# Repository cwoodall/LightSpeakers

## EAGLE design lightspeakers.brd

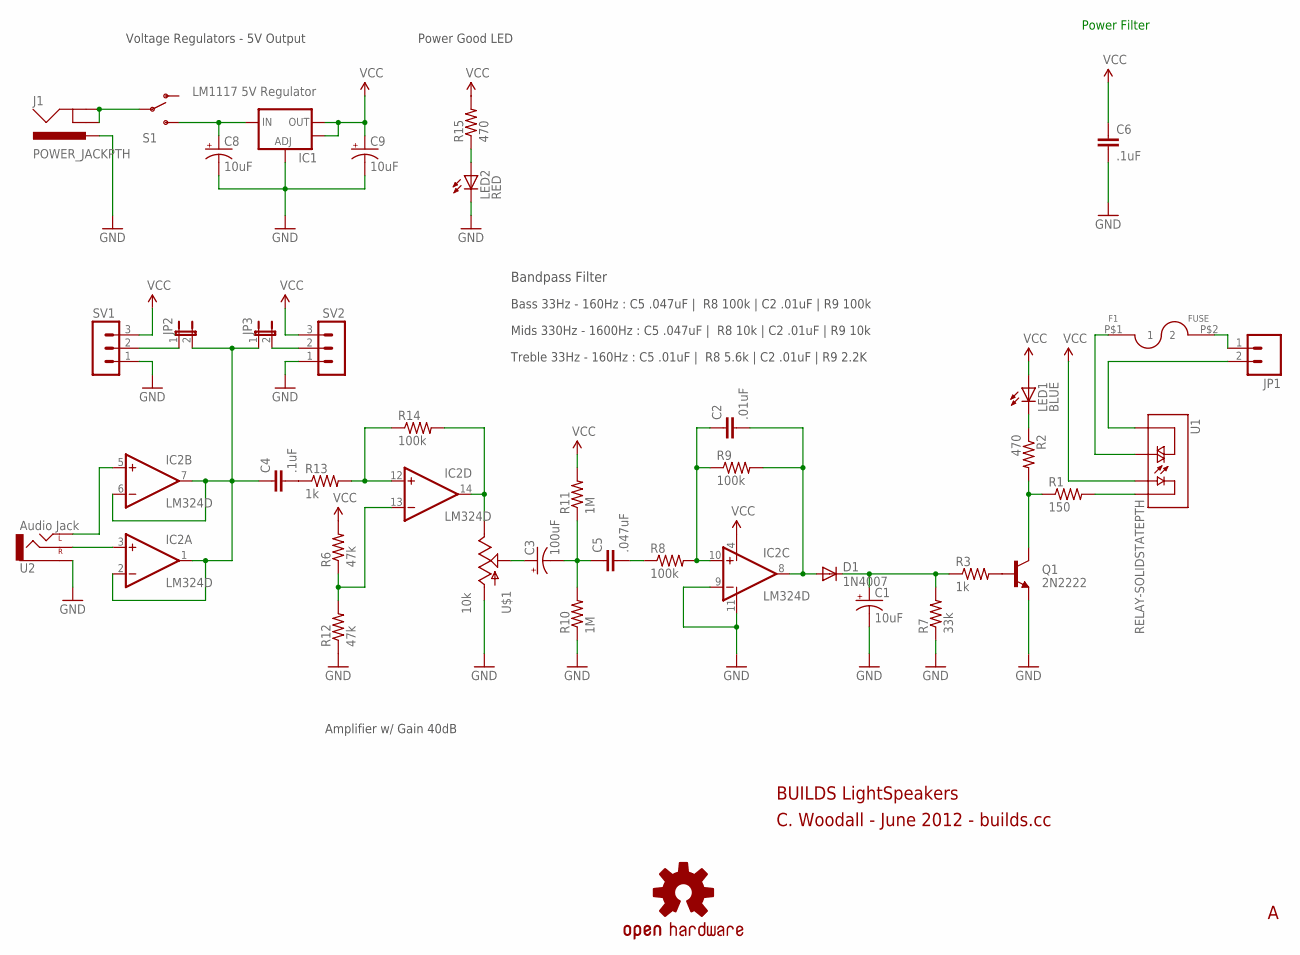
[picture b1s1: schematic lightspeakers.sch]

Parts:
C1, C8, C9: 10uF; CPOL-RADIAL-10UF-25V
C2: .01uF; 0603-CAP
C3: 100uF; CPOL-RADIAL-100UF-25V
C4, C6: .1uF; 0603-CAP
C5: .047uF; 0603-CAP
D1: 1N4007; DIODE-1N4001
F1: FUSE; 20MMX5MMFUSE
IC1: LM1117 5V Regulator; SOT223
IC2: LM324D; SO14
J1: POWER_JACKPTH; POWER_JACK_PTH
JP1: M025MM; SCREWTERMINAL-5MM-2
JP2, JP3: JUMPER-2PTH; 1X02
LED1: BLUE; LED-0603
LED2: RED; LED-0603
Q1: 2N2222; TO-92-AMMO
R1: 150; 0603-RES
R2, R15: 470; 0603-RES
R3, R13: 1k; 0603-RES
R6, R12: 47k; 0603-RES
R7: 33k; 0603-RES
R8, R9, R14: 100k; 0603-RES
R10, R11: 1M; 0603-RES
S1: SWITCH-SPSTPTH; SWITCH-SPDT
SV1, SV2: MA03-1
U1: RELAY-SOLIDSTATEPTH; RELAY-S108T02
U2: Audio Jack; AUDIO-JACK
U$1: 10k; 3362U
U$2: OSHW-LOGOS; OSHW-LOGO-S

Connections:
GND: C1.2 (-), C6.2, C8.2 (-), C9.2 (-), IC1.1 (ADJ), IC2.9 (-IN), IC2.11 (V-), J1.PWR, LED2.C, Q1.1 (E), R7.1, R10.1, R12.1, SV1.1, SV2.1, U2.SLEEVE, U$1.P$3 (A)
unnamed: Q1.3 (C), R1.1, R2.2
unnamed: R1.2, U1.4 (-)
unnamed: F1.P$1 (1), U1.2 (T2)
unnamed: Q1.2 (B), R3.2
unnamed: LED1.C, R2.1
unnamed: C5.2, R8.1
unnamed: C1.1 (+), D1.C, R3.1, R7.2
unnamed: C2.2, D1.A, IC2.8 (OUT), R9.2
unnamed: C2.1, IC2.10 (+IN), R8.2, R9.1
unnamed: C3.2 (-), C5.1, R10.2, R11.1
unnamed: C3.1 (+), U$1.P$2 (S)
unnamed: C4.2, R13.1
unnamed: JP3.2, SV2.2
unnamed: LED2.A, R15.1
unnamed: J1.GND, J1.GNDBREAK, S1.2
unnamed: IC2.13 (-IN), R6.1, R12.2
unnamed: IC2.14 (OUT), R14.2, U$1.P$1 (E)
unnamed: IC2.12 (+IN), R13.2, R14.1
unnamed: JP2.1, SV1.2
unnamed: C8.1 (+), IC1.3 (IN), S1.3 (S)
unnamed: IC2.5 (+IN), U2.TIP (LEFT)
unnamed: C4.1, IC2.1 (OUT), IC2.2 (-IN), IC2.6 (-IN), IC2.7 (OUT), JP2.2, JP3.1
unnamed: IC2.3 (+IN), U2.RING (RIGHT)
unnamed: JP1.2, U1.1 (T1)
unnamed: F1.P$2 (2), JP1.1
VCC: C6.1, C9.1 (+), IC1.2 (OUT), IC1.4 (OUT), IC2.4 (V+), LED1.A, R6.2, R11.2, R15.2, SV1.3, SV2.3, U1.3 (+)

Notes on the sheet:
Power Filter
Power Good LED
Voltage Regulators - 5V Output
Amplifier w/ Gain 40dB
Bandpass Filter
Bass 33Hz - 160Hz : C5 .047uF | R8 100k | C2 .01uF | R9 100k
Treble 33Hz - 160Hz : C5 .01uF | R8 5.6k | C2 .01uF | R9 2.2K
Mids 330Hz - 1600Hz : C5 .047uF | R8 10k | C2 .01uF | R9 10k
BUILDS LightSpeakers
C. Woodall - June 2012 - builds.cc

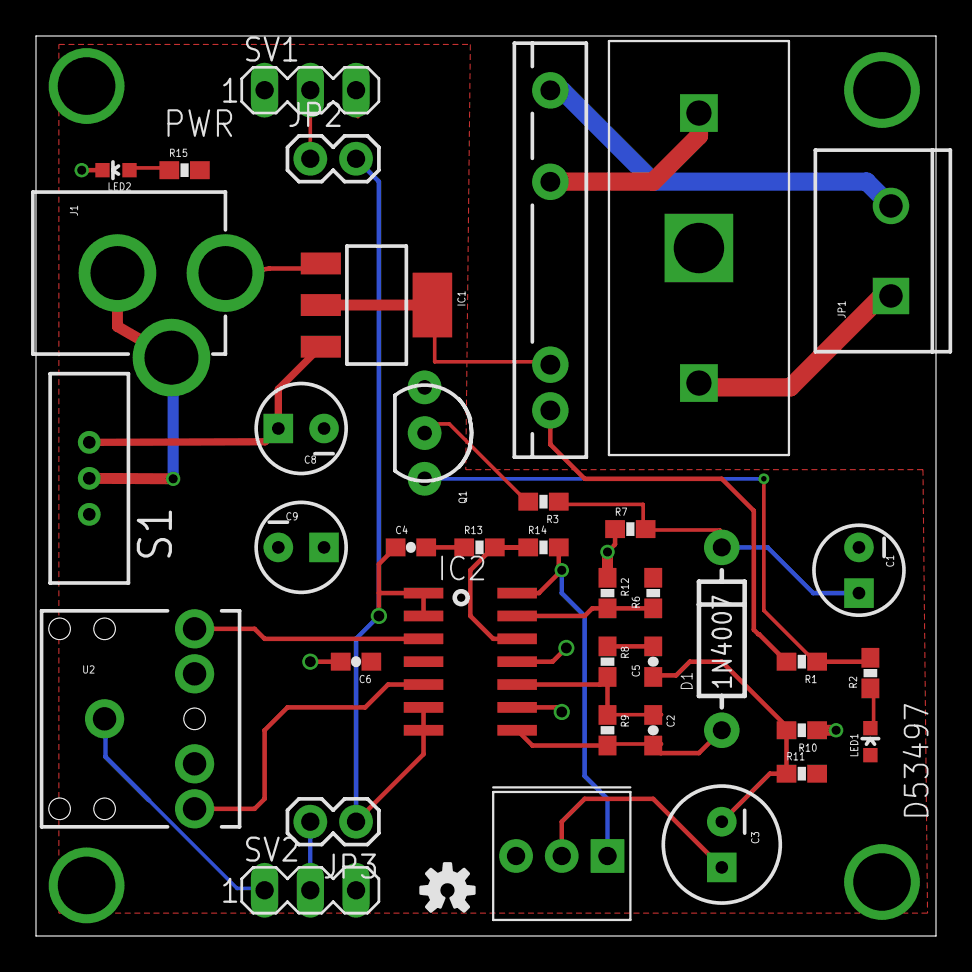
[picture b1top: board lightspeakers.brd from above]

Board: 2 copper layers, 50.0 x 50.0 mm, 39 parts (0 on the bottom side), 27 nets.

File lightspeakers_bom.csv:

,,,,,,
"Part","Value","Distributor","Distributor Number","Manufacturer","Manufacturer Number","Unit Price"
"C1,C8","10uF Electrolytic","Digikey","P10404TB-ND",,,0.2
"C2",".01uF 603","Digikey","490-1512-1-ND",,,0.023
"C3","100uF Electrolytic","Digikey","P15348CT-ND",,,0.49
"C4, C6",".1uF 603","Digikey","490-1532-1-ND",,,0.023
"C5",".047uF 603","Digikey","490-1567-1-ND",,,0.041
"C8, C9","10uF EIA6032","Digikey","495-2260-1-ND",,,0.65
"D1","1N4001","Digikey","1N4001-E3/54GICT-ND","Vishay","1N4001-E3/54",0.43
"IC1","LM1117 5V Regulator","Digikey","LM1117MPX-5.0CT-ND","National","LM1117MPX-5.0/NOPB",1.16
"IC3","LM358 SOIC8","Digikey","LM358MXRCT-ND","Rohm","LM358MX",0.76
"J1","Power Jack","Digikey","CP-202A-ND","CUI Inc","PJ-202A",0.092
"J2","Terminal Block (2x)","Digikey","ED1623-ND",,,0.59
"JP2",".1” Headers","stock","stock","stock","stock",0
"JP3",".1” Headers","stock","stock","stock","stock",0
"LED1","LED BLUE 603","Digikey","P2N2222AGOS-ND","Lite-On","LTST-C191TBKT",0.5
"LED2","LED RED 603","Digikey","751-1182-1-ND","Vishay","TLMS1100-GS08",0.5
"Q1","2n2222 TO-92","Digikey","P2N2222AGOS-ND","ON Semiconductor","P2N2222AG",0.36
"R1","150 603","Digikey","ERJ-3GEYJ151V","Panasonic",,0.1
"R2, R15","470 603","Digikey","ERJ-3GEYJ471V","Panasonic",,0.1
"R3, R13","2.2k 603","Digikey","ERJ-3GEYJ222V","Panasonic",,0.1
"R6,R12","47k 603","Digikey","ERJ-3GEYJ473V","Panasonic",,0.1
"R7","33k 603","Digikey","ERJ-3GEYJ333V","Panasonic",,0.1
"R8, R9, R14","100k 603","Digikey","ERJ-3GEYJ104V","Panasonic",,0.1
"R10, R11","1M 603","Digikey","ERJ-3GEYJ105V","Panasonic",,0.1
"S1","SWITCH-SPSTSMD2","Digikey","450-1635-ND","TE","SSJ12R04",0.79
"SV1",".1” Headers Male Right Angle","stock","stock",,,0
"SV2",".1” Headers Female Right Angle","Digikey","S5439-ND",,,0.65
"U$1","10k Pot 3362U","Digikey","3362U-103LF-ND","Bourns Inc.","3362U-1-103LF",1.05
"U1","SSR S108T02","Digikey","425-2396-5-ND","Sharp Micro","S108T02F",5.01
"U2","3.5mm Audio Jack","Digikey","CP1-3524NG-ND","CUI Inc","SJ1-3524NG",0.85
,,,,,,
,,,,,,
,,,,,,
"Total Cost",14.869,,,,,

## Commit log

2012-06-02 Changed isolation to 16mil
2012-06-23 Finished PCB, added fuse, sending out
2012-06-23 Sent off to the board house, SEEED Studio, lets see how it comes out
2012-06-25 Updated BOM

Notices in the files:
parts and their libraries:
SparkFun: Licensing: CC v3.0 Share-Alike You are welcome to use this library for commercial purposes.
